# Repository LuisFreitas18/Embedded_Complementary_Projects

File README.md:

# 🛠️ Embedded Complementary Projects

)

📦 Repositório pessoal com pequenos projetos de *sistemas embarcados (embedded)*, hardware e eletrónica aplicada.

Serve como arquivo de aprendizagem, prototipagem e também como base para voltar a usar estes circuitos e sketches mais tarde, sem ter de começar do zero.

---

## 🎛️ Plataformas

| Categoria                    | Tecnologias Aplicadas                                                                |
| :--------------------------- | :----------------------------------------------------------------------------------- |
| **Microcontroladores** | Raspberry Pi Pico (RP2040), Espressif ESP32 (WROOM-32), ATTINY (85)                  |
| **Frameworks & IDEs**  | Arduino Framework, ESP-IDF Framework, PlatformIO, VS Code                            |
| **CAD Eletrónica**    | KiCad (Esquemáticos e Simulação)                                                  |
| **Linguagens**         | C/C++ (Firmware), Python (Scripts de Automação / Deploy / Pre&Post platformio.ini) |

---

## 📂 Projetos

O repositório está organizado no formato de **Monorepo**, com divisão dos projetos por arquitetura de hardware:

### 🌐 ESP32

* **[httphost_esp32](./ESP32/httphost_esp32):** Servidor HTTP minimalista nativo para controlo remoto de IOs e monitorização de estado via Wi-Fi.
* **[ws_ap_matrix_esp32](./ESP32/ws_ap_matrix_esp32):** Aplicação Web embarcada para ESP32 em ESP-IDF que permite controlar e sincronizar bidirecionalmente uma matriz 2D em tempo real via WebSockets. Mantem os dados persistentes na memória NVS.
* **[esp32-idf_ota](./ESP32/esp32-idf_ota):** Implementação de atualização over-the-air (OTA) para ESP32 com a framework ESP-IDF. Interface web para upload de firmware, com verificação de integridade e rollback automático em caso de falha.
* **[ElegantOTA_esp32](./ESP32/ElegantOTA_esp32):** Implementação de atualização over-the-air (OTA) para ESP32 com a framework Arduino e library ElegantOTA.

### 📌 RP2040 (Pi Pico)

* **[pwm_led_dc-motor_1mosfet](./RP2040/pwm_led_dc-motor_1mosfet):** Controlo de velocidade de motor DC e brilho de LEDs por PWM, com utilização de encoders rotativos e isolamento com optoacopladores de alta velocidade (6N137).
* **[i2110_h-bridge_4mosfets_w-leds](./RP2040/i2110_h-bridge_4mosfets_w-leds):** Implementação de uma ponte H discreta com 4 MOSFETs de canal N, com utilização de drivers de Gate IR2110 para controlo de inversão de marcha e travagem de motores.
* **[blow_capacitor](./RP2040/blow_capacitor/blow_capacitor):** O objetivo é literalmente explodir um condensador eletrolítico de 22µF / 100V injetando-lhe 220VAC da rede elétrica através de um relé, tudo acionado em segurança via comando de Infravermelhos (IR).

### 𓇲 ATTINY (85)

* **[ArduinoISP_program_attitny85_using_esp32](./ATTINY/ArduinoISP_program_attitny85_using_esp32):** 2 módulos PlatformIO: Utilizar o ESP32 como programador ArduinoISP para fazer upload de código para ATTINY, neste caso Attiny85; Código de teste simples LED Blink para testar o funcionamento do ATTINY programado com ESP32 ArduinoISP. `platformio.ini` oferece configurações para o clock do Attiny85.

### ⤮  Platform Crossover

* **[ws_ap_matrix_esp32+rp2040_HALimplementation_env](./MCU_PlatformCrossover/ws_ap_matrix_esp32+rp2040_HALimplementation_env):** Protótipo cross-platform (ESP32 / Pi Pico W) com camada Hardware Abstraction Layer (HAL), controlo de matriz 2D via WebSockets, exemplos de armazenamento em BLOB matriz e struct (NVS) e scripts Python para load de credenciais (.env).

### 🪫 Sem MCU, apenas eletrónica e circuitos

* **[boost_converter_UC3843_5Vto12V](./NO_MCU(ElectronicsOnly)/boost_converter_UC3843_5Vto12V):** Conversor Boost (Step-Up) de 5V para 12V, baseado no controlador PWM UC3843. Implementação de um conversor DC-DC THT, capaz de elevar uma tensão de entrada de 5V (por exemplo, de uma porta USB2.0) para uma saída regulada de 12V. Inclui esquemáticos, layout de PCB e render 3D (KiCad).

---

## ⚙️ Miscellaneous

### 🚀 Upload Automático para o Pi Pico via Python

Por padrão, o PlatformIO tenta enviar o código para o Pi Pico usando uma porta COM (Serial). Mas quando metes o Pico em modo **BOOTSEL**, ele vira uma pen USB (`RPI-RP2`), o que faz o upload normal falhar.

Para resolver isso, criei um script em Python que faz tudo sozinho:

1. Altera o comportamento do PlatformIO para o modo de upload customizado.
2. Sempre que clicas no botão **Upload**, o script Python entra em ação, deteta automaticamente a drive do Pico (no Windows, Linux ou Mac) e injeta lá o ficheiro `.uf2` compilado.
3. Dá-te feedback com cores vivas no terminal para saberes se correu bem.

Basicamente, passas a ter um botão de Upload funcional via USB Mass Storage sem teres de arrastar ficheiros à mão.

### 🔐 Credenciais em (.env) via Python

Para evitar expor o SSID e a Palavra-passe do Access Point (AP) no controlo de versão (Git), a configuração de rede é injetada automaticamente durante o processo de compilação:

1. O script `load_ap_env.py` é executado antes da compilação iniciar (`extra_scripts = pre:load_ap_env.py`) e lê o ficheiro privado `src/.env`.
2. Gera automaticamente o cabeçalho C `src/ap_config.h` com os `#define` contendo o SSID e a palavra-passe lidos.
3. Garante que as credenciais reais ficam protegidas e fora do repositório, disponibilizando apenas o modelo público `.env.example`.

---

## 🚀 Clonar e Configurar

Para evitar conflitos de compilação entre o Plataformas diferentes, este repositório utiliza **Multi-root Workspaces** do VS Code.

1. Faz o clone do repositório para a tua máquina:

   ```bash
   git clone [https://github.com/LuisFreitas18/Embedded_Complementary_Projects.git](https://github.com/LuisFreitas18/Embedded_Complementary_Projects.git)
   ```
2. No VS Code, vai a **File ➔ Open Workspace from File...** e escolhe o ficheiro:
   `Embedded_Complementary_Projects.code-workspace`

Cada projeto vai aparecer como uma pasta separada na barra lateral e PlatformIO vai reconhecer tudo.

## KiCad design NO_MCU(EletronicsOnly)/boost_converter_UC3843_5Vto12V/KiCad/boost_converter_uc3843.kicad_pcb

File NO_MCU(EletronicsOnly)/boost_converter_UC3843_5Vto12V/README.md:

# ⚡ Conversor Boost (Step-Up) 5V para 12V com UC3843

Este projeto detalha a implementação de um conversor DC-DC Boost (Step-Up) que eleva uma tensão de entrada de 5V (ideal para ser alimentado via USB 2.0) para uma saída regulada de 12V. O circuito é baseado no popular controlador PWM UC3843, conhecido pela sua robustez e eficiência em aplicações de comutação.

## 📝 Resumo do Projeto

Fornecer uma fonte de alimentação de 12V estável a partir de uma fonte de 5V, útil para alimentar diversos módulos e componentes eletrónicos que requerem uma tensão mais elevada. O design tem de considerar as regras para um circuito de potência, como seleção de componentes, layout de PCB e dissipação térmica.

## 🎨 Design KiCad

### 💡 Esquema Elétrico

O esquema elétrico detalha a interconexão de todos os componentes, incluindo o controlador UC3843, MOSFET de potência, díodos Schottky, indutor e condensadores de filtro.

### 🗺️ Layout da PCB

A PCB foi desenhada para otimizar o desempenho do conversor, minimizando ruído e perdas. Abaixo, pode ver o layout com e sem o plano de terra (ground plane).

**Com Ground Plane:**

**Sem Ground Plane:**

### 📦 Vista 3D do Circuito

Uma renderização 3D da placa montada para visualização do aspeto final do circuito.

## 📊 Lista de Materiais (BOM)

A lista completa de componentes pode ser encontrada nos seguintes ficheiros:

* [KiCad BOM (CSV)](KiCad/boost_converter_uc3843.csv)
* [Farnell BOM (Excel)](KiCad/boost_converter_uc3843.xls)

## 🔎 Componentes Chave

Alguns dos componentes mais importantes utilizados neste projeto:

* **Controlador PWM UC3843BN:**
  
* **Indutor 33470C:**
  
* **MOSFET IRLZ44NPBF:**
  
* **Díodo Schottky 1N5822:**

## ⚙️ Como funciona o UC3843

O UC3843BN é um controlador PWM de modo de corrente. Em cada ciclo de comutação, o controlador liga o MOSFET e acompanha a corrente através do shunt. Quando a corrente atinge o nível determinado pelo sinal de realimentação, o pulso é desligado.

O UC3843 controla o IRLZ44N. Quando o MOSFET conduz, a corrente aumenta no indutor 33470C e é armazenada energia no seu campo magnético. Quando o MOSFET desliga, essa energia passa pelo díodo Schottky 1N5822 para os condensadores e para a carga, elevando a tensão de 5V para aproximadamente 12V.

O modo de corrente tem algumas vantagens importantes:

- permite controlar diretamente a corrente de pico no MOSFET e no indutor;
- melhora a resposta do conversor a alterações de carga;
- permite implementar proteção ciclo a ciclo através da entrada `ISENSE`;
- facilita a compensação da malha de controlo relativamente a um PWM apenas baseado em tensão.

O UC3843 inclui ainda uma referência interna de 5V, amplificador de erro, oscilador, entrada de limitação de corrente e uma saída de driver capaz de fornecer e absorver corrente para comandar um MOSFET. A frequência indicada neste projeto é de 500 kHz.

### Alimentação e arranque

Uma particularidade importante é que o UC3843 não arranca simplesmente ligado aos 5V de entrada. A tensão `VCC` tem de ultrapassar aproximadamente 8,4V para sair do bloqueio de subtensão (`UVLO`). Depois de arrancar, o circuito deve manter a alimentação acima do limiar de desligamento, que é tipicamente próximo de 7,6V.

Por essa razão, o esquema prevê um bootstrap indutivo. Durante o arranque é necessário garantir que `VCC` atinge o valor mínimo; depois, a alimentação auxiliar obtida a partir da comutação mantém o controlador ativo. Este ponto deve ser confirmado no protótipo com um osciloscópio, medindo `VCC` desde o instante em que se aplica a alimentação.

### Duty cycle e correntes

Para uma primeira aproximação ideal de 5V para 12V, o duty cycle necessário é:

```text
D = 1 - (Vin / Vout) = 1 - (5 / 12) = 58,3%
```

Na prática, o duty cycle será superior devido às perdas no MOSFET, no díodo, no indutor e nas pistas da PCB. A corrente de entrada pode ser bastante elevada: uma saída de 12V com 1A, por exemplo, já exige mais de 2,4A na entrada considerando uma eficiência de 80%. A corrente real disponível na saída deve, por isso, ser validada com medições e não apenas calculada a partir da tensão nominal.

### Layout e caminhos de potência

- manter muito curto o caminho de corrente pulsada entre o indutor, o MOSFET, o díodo e os condensadores de saída;
- usar pistas largas para a entrada, a saída e o retorno de corrente de potência;
- colocar os condensadores de desacoplamento junto dos pinos `VCC` e `GND` do UC3843;
- manter o caminho do gate entre o pino `OUTPUT`, a resistência de gate e o MOSFET curto;
- separar a massa de potência da massa de sinal e uni-las num ponto controlado, próximo do shunt ou conforme indicado no esquema;
- evitar que pistas de potência comutadas passem junto da entrada `ISENSE`, da realimentação e do oscilador.

O plano de massa ajuda a reduzir a impedância do retorno e o ruído, mas não deve criar um caminho de retorno inesperado sob o nó de comutação. A área de cobre ligada ao dreno do MOSFET deve ser mantida tão pequena quanto possível para reduzir interferência eletromagnética.

### Medição de corrente e controlo

O shunt de 0,1 Ω produz uma tensão proporcional à corrente do MOSFET. As pistas que vão para `ISENSE` devem ser curtas e, idealmente, ligadas diretamente aos terminais do shunt através de uma ligação Kelvin. Não se deve recolher este sinal a partir de uma pista que também transporte a corrente de potência.

O sinal de `ISENSE` pode ter picos rápidos causados pela comutação. Um pequeno filtro RC pode ser necessário, mas deve ser dimensionado com cuidado para não atrasar demasiado a proteção de sobrecorrente. A compensação ligada ao amplificador de erro também deve ser ajustada com medições de estabilidade, resposta transitória e ondulação da saída.

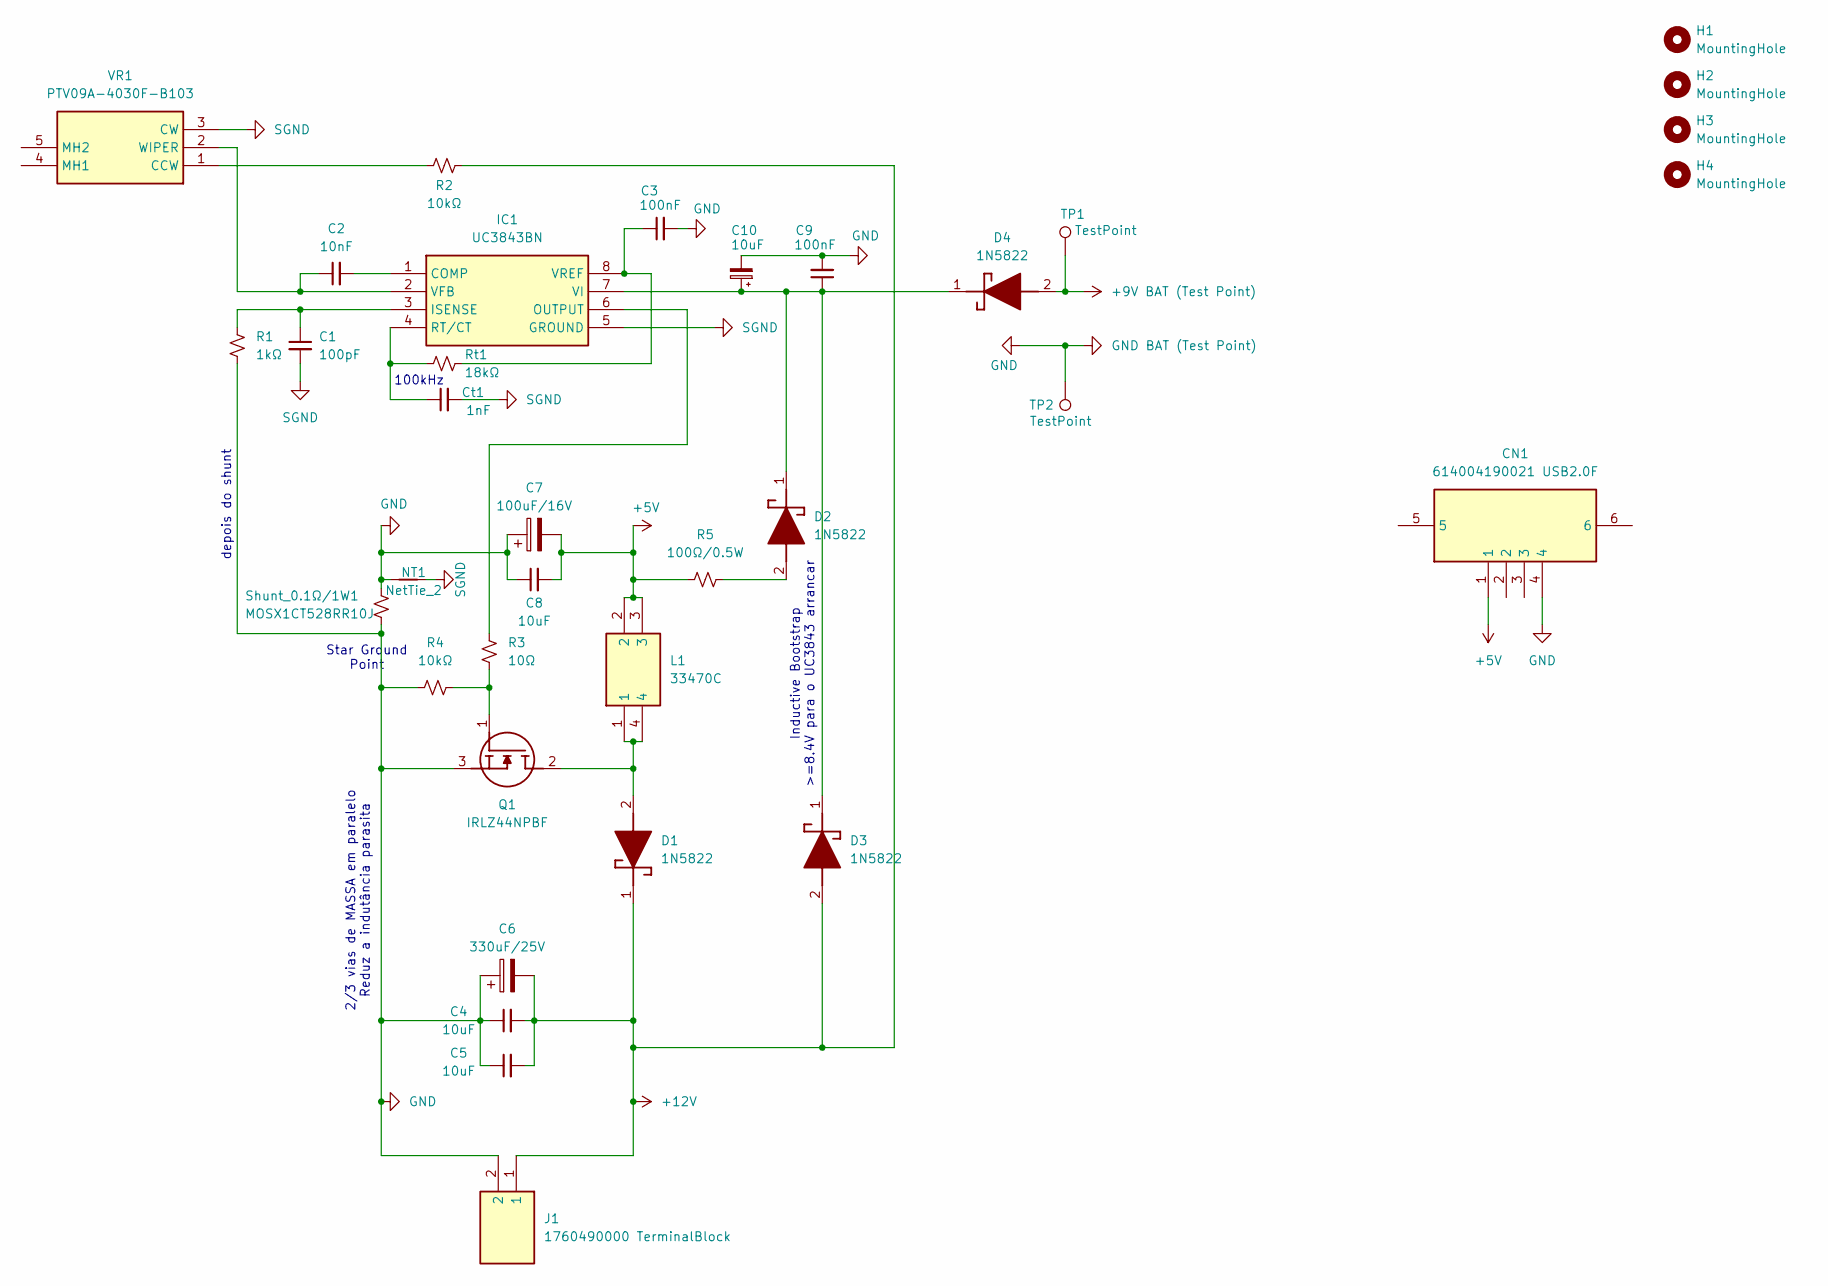
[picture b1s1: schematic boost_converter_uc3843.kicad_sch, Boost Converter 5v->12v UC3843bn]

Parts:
C1: 100pF; C_Disc_D5.0mm_W2.5mm_P5.00mm
C2: 10nF; C_Disc_D5.0mm_W2.5mm_P5.00mm
C3, C9: 100nF; C_Disc_D5.0mm_W2.5mm_P5.00mm
C4, C5, C8, C10: 10uF; CP_Radial_D6.3mm_P2.50mm
C6: 330uF/25V; CP_Radial_D8.0mm_P3.50mm
C7: 100uF/16V; CP_Radial_D6.3mm_P2.50mm
CN1: 614004190021 USB2.0F; USB-2.0-TYPE-A; Manufacturer_Part_Number 614004190021
Ct1: 1nF; C_Disc_D5.0mm_W2.5mm_P5.00mm
D1, D2, D3, D4: 1N5822; DIOAD3070W130L950D530; Manufacturer_Part_Number 1N5822
H1, H2, H3, H4: MountingHole; MountingHole_3.2mm_M3
IC1: UC3843BN; DIP762W55P254L1092H508Q8N; Manufacturer_Part_Number UC3843BN
J1: 1760490000 TerminalBlock; 1760490000; Manufacturer_Part_Number 1760490000
L1: 33470C; Manufacturer_Part_Number 33470C
NT1: NetTie_2; NetTie-2_THT_Pad1.0mm
Q1: IRLZ44NPBF; TO254P469X1042X1967-3P; Manufacturer_Part_Number IRLZ44NPBF
R1: 1kΩ; R_Axial_DIN0207_L6.3mm_D2.5mm_P10.16mm_Horizontal
R2, R4: 10kΩ; R_Axial_DIN0207_L6.3mm_D2.5mm_P10.16mm_Horizontal
R3: 10Ω; R_Axial_DIN0207_L6.3mm_D2.5mm_P10.16mm_Horizontal
R5: 100Ω/0.5W; R_Axial_DIN0411_L9.9mm_D3.6mm_P12.70mm_Horizontal
Rt1: 18kΩ; R_Axial_DIN0207_L6.3mm_D2.5mm_P10.16mm_Horizontal
Shunt_0.1Ω/1W1: MOSX1CT528RR10J; R_Axial_DIN0414_L11.9mm_D4.5mm_P15.24mm_Horizontal
TP1, TP2: TestPoint; TestPoint_THTPad_D1.0mm_Drill0.5mm
VR1: PTV09A-4030F-B103; PTV09A4030FB103; Manufacturer_Part_Number PTV09A-4030F-B103

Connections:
+5V: C7.2, C8.2, CN1.1, L1.2, L1.3, R5.2
+9V BAT (Test Point): D4.2 (A), TP1.1 (1_1)
+12V: C4.2, C5.2, C6.2, D1.1 (K), D3.2 (A), J1.1, R2.1
GND: C3.2, C4.1, C5.1, C6.1, C7.1, C8.1, C9.2, C10.2, CN1.4, J1.2, NT1.1, Q1.3 (S), R1.1, R4.2, Shunt_0.1Ω/1W1.1, Shunt_0.1Ω/1W1.2, TP2.1 (1_1)
unnamed: D1.2 (A), L1.1, L1.4, Q1.2 (D)
unnamed: D2.2 (A), R5.1
unnamed: C9.1, C10.1, D2.1 (K), D3.1 (K), D4.1 (K), IC1.7 (VI)
unnamed: C2.2, IC1.1 (COMP)
unnamed: C1.1, IC1.3 (ISENSE), R1.2
unnamed: IC1.6 (OUTPUT), R3.2
unnamed: Ct1.1, IC1.4 (RT/CT), Rt1.2
unnamed: C2.1, IC1.2 (VFB), VR1.2 (WIPER)
unnamed: C3.1, IC1.8 (VREF), Rt1.1
unnamed: Q1.1 (G), R3.1, R4.1
unnamed: R2.2, VR1.1 (CCW)
SGND: C1.2, Ct1.2, IC1.5 (GROUND), NT1.2, VR1.3 (CW)

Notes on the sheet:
depois do shunt
2/3 vias de MASSA em paralelo Reduz a indutância parasita
100kHz
Inductive Bootstrap >=8.4V para o UC3843 arrancar
Star Ground Point

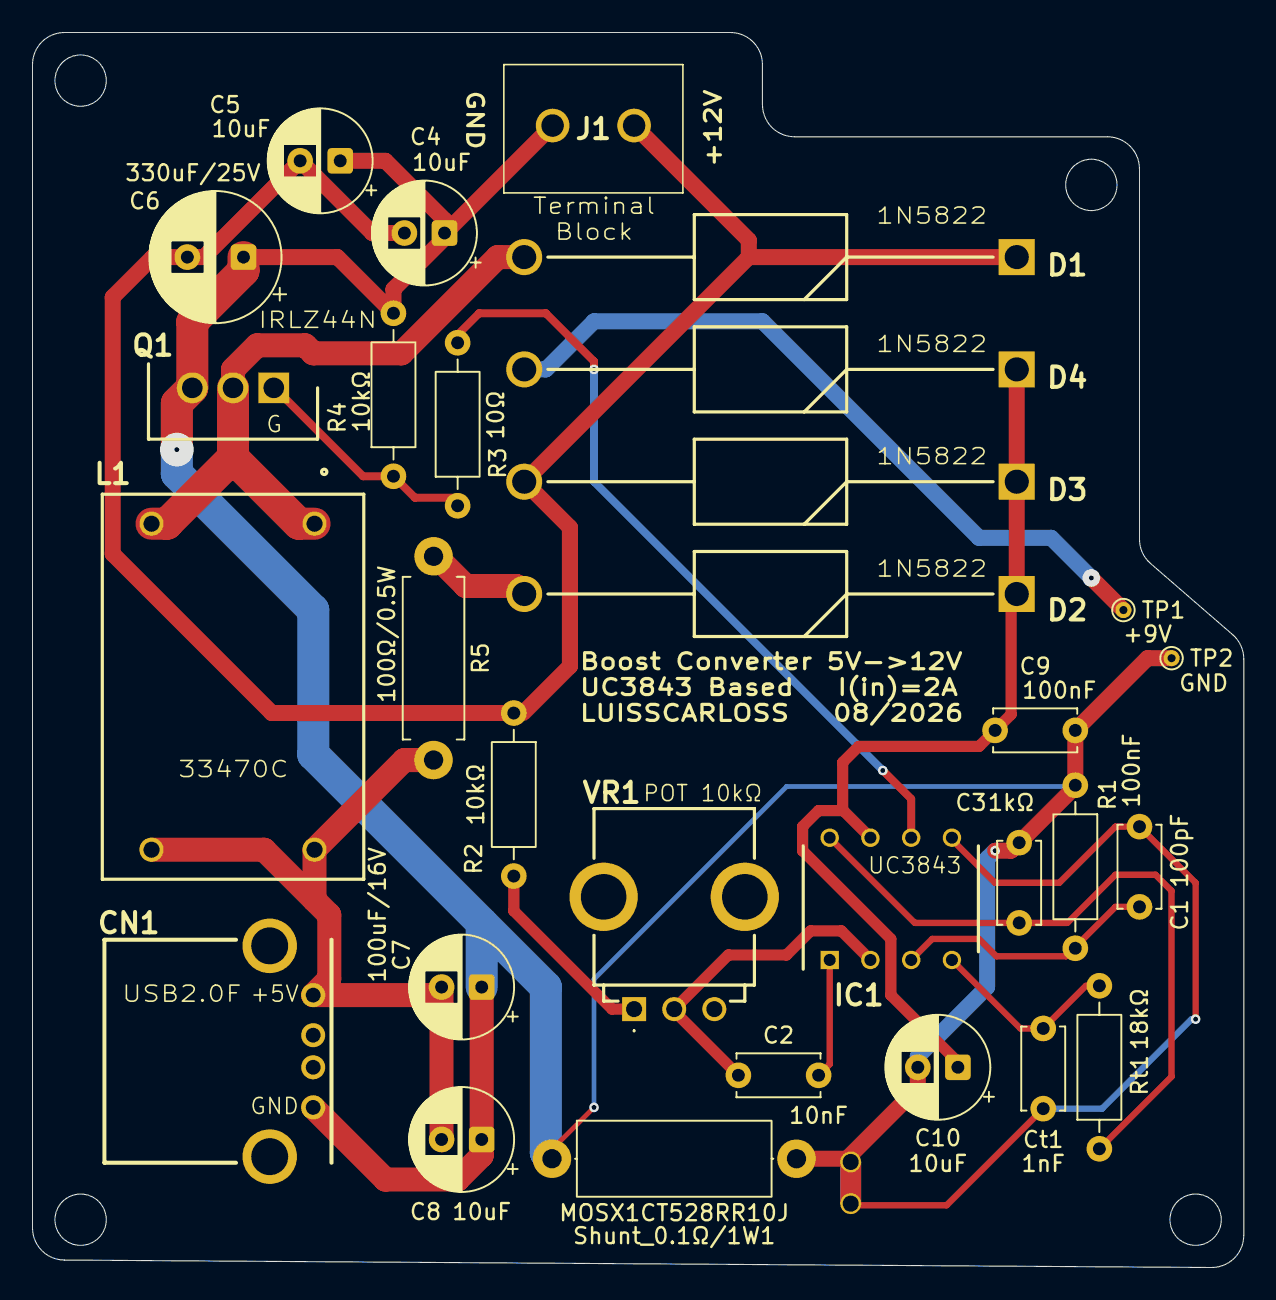
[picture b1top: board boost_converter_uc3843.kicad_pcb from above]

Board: 2 copper layers, 75.5 x 77.0 mm, 35 parts (0 on the bottom side), 16 nets.

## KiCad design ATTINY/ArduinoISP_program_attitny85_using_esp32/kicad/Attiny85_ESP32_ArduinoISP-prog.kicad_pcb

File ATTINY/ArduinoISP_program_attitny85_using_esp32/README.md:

# ArduinoISP_program_attitny85_using_esp32

Projeto para utilizar um ESP32 como programador ArduinoISP para um microcontrolador ATTiny85.

## Montagem

## Esquemáticos e PCB KiCad

- [Esquema em PDF](kicad/Attiny85_ESP32_ArduinoISP-prog.pdf)
- [Ficheiro de esquema KiCad](kicad/Attiny85_ESP32_ArduinoISP-prog.kicad_sch)
- [Ficheiro de PCB KiCad](kicad/Attiny85_ESP32_ArduinoISP-prog.kicad_pcb)
- [Visualização 3D da PCB](kicad/Attiny85_ESP32_ArduinoISP-prog.step)

## O que este projeto faz

- Transforma um ESP32 num programador ISP (In-System Programmer) compatível com o protocolo ArduinoISP.
- Permite carregar firmware para um ATTiny85 utilizando a IDE Arduino ou PlatformIO.

## Pinagem (ESP32 para ATTiny85)

- **ESP32_SCK (GPIO 18)** -> **ATTiny85_SCK (Pin 2 / PB2)**
- **ESP32_MOSI (GPIO 23)** -> **ATTiny85_MOSI (Pin 5 / PB0)**
- **ESP32_MISO (GPIO 19)** -> **ATTiny85_MISO (Pin 6 / PB1)**
- **ESP32_RST (GPIO 5)** -> **ATTiny85_RST (Pin 1 / PB5)**
- **ESP32_GND** -> **ATTiny85_GND (Pin 4)**
- **ESP32_VCC (3.3V)** -> **ATTiny85_VCC (Pin 8)**

## Ficheiros principais

### Firmware do ESP32 (ArduinoISP)
- [main.cpp](ArduinoISP_program_attitny85_using_esp32_PlatformIO/src/main.cpp)
- [platformio.ini](ArduinoISP_program_attitny85_using_esp32_PlatformIO/platformio.ini)

### Exemplo de Firmware para ATTiny85 (LED Blink)
- [main.cpp](Attiny85_LEDblink_esp32_as_ISP_PlatformIO/src/main.cpp)
- [platformio.ini](Attiny85_LEDblink_esp32_as_ISP_PlatformIO/platformio.ini)

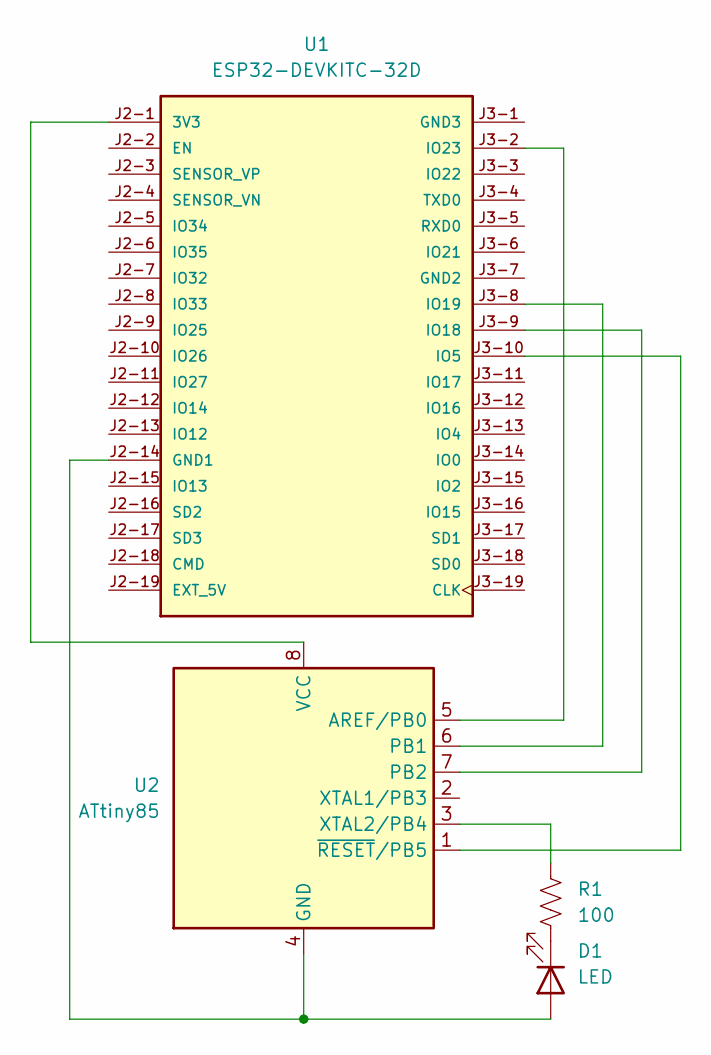
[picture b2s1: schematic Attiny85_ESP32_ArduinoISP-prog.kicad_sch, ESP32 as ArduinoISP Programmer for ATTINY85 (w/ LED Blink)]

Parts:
D1: LED; LED_D4.0mm
R1: 100; R_Axial_DIN0204_L3.6mm_D1.6mm_P5.08mm_Horizontal
U1: ESP32-DEVKITC-32D; MODULE_ESP32-DEVKITC-32D; PARTREV V4
U2: ATtiny85; DIP-8_W7.62mm

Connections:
unnamed: D1.2 (A), U1.J2-14 (GND1), U2.4 (GND)
unnamed: D1.1 (K), R1.1
unnamed: U1.J2-1 (3V3), U2.8 (VCC)
unnamed: U1.J3-10 (IO5), U2.1 (~RESET/PB5)
unnamed: U1.J3-9 (IO18), U2.7 (PB2)
unnamed: U1.J3-8 (IO19), U2.6 (PB1)
unnamed: U1.J3-2 (IO23), U2.5 (AREF/PB0)
unnamed: R1.2, U2.3 (XTAL2/PB4)

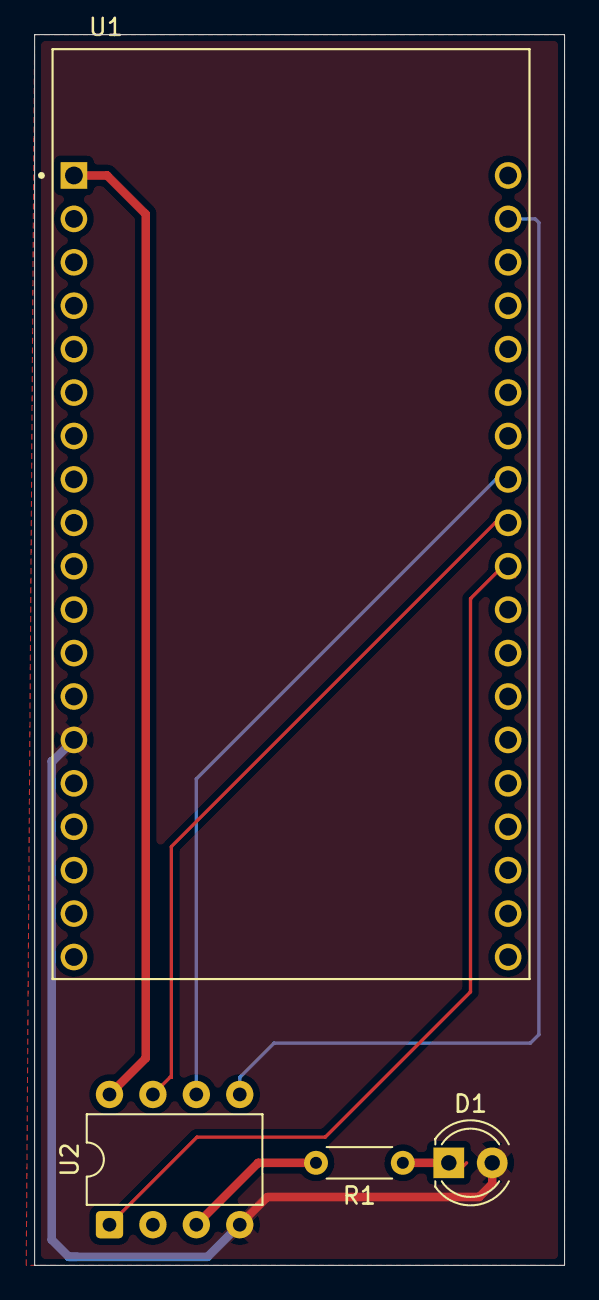
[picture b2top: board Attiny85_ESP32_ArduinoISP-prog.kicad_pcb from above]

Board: 2 copper layers, 31.0 x 72.0 mm, 4 parts (0 on the bottom side), 8 nets.
